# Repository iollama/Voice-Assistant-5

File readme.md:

# Voice Assistant 5 — STEM Oriented ESP32 Voice Assistant With No Personality

Press the button, talk, let go — and get an instant spoken reply, with an animated emoji face that grins, frowns and laughs along with the conversation. Less than $20 in parts, a case you print yourself, running on your own OpenAI key.

The part that makes it worth building: **it has no character until you give it one.**

Everything that gives this thing a personality lives behind a web page the device serves. The ~~system~~ persona prompt, one of ten voices, the spoken language, and the face itself:
drop in a GIF, PNG, JPG or MP4 and it adopts immediately. No recompile, no cable, no SD card, no code. Write Nietzsche. Write Churchill. Write Daffy Duck. Hand it to someone else and let them write over it.

That design came out of a classroom. VA5 is used in schools, where students research a figure, write the persona themselves, load it on, and then have to
hold a conversation with what they wrote. A thin characterisation falls apart within a minute or two of being interrogated, so they go back and rewrite it.
Write, test by talking, revise — which is prompt engineering, except nobody has to call it that.

Thirty students cannot each be flashing firmware. That single constraint explains most of the design decisions in this repo: why the whole persona is editable from a phone, and why personas export as a `.zip` so one set of
devices can cycle between classes.

## Features

- **Press to talk, get an instant reply** -- hold the button to speak, release and it answers right back (no wake word, no waiting)
- **Animated emoji face shows you how the assistant feels** -- the assistant itself picks the mood and the display reacts in real time
- **Control the assistant personality** -- write who it is and how it behaves, right from your phone, no code needed
- **Glance to know what it's doing** -- a colored light tells you when it's listening, thinking, or speaking
- **The assistant adjusts its own volume** -- say "speak up" or "quieter please" and it adjusts in real time; the new level persists across reboots
- **Plug in your own OpenAI key** -- you control the account and the cost, no subscription in the middle
- **Make the face your own** -- drop in a GIF, PNG, JPG, or MP4 from the web portal and the assistant uses it as the on-device emoji; reset back to the defaults any time
- **It remembers the conversation** -- pick up where you left off instead of starting from scratch
- **Set up WiFi once, anywhere** -- connect from your phone the first time; it remembers up to 6 networks and picks the right one wherever you take it
- **Build it yourself for ~$20** -- 3D-printed case included, full source open and hackable, parts links provided

## Initial Setup

1. **Connect to the device's WiFi.** On first boot the assistant creates an open WiFi network named `VOICE-AGENT-XXYY` (the `XXYY` is the last 2 bytes of its MAC address). No password.
2. **Set your home WiFi.** Your phone should pop the captive portal automatically -- if not, open a browser and go to `http://192.168.4.1`. Under **Wi-Fi Networks**, enter your network name and password, hit **Add network**, then **Connect & reboot**. The device remembers it from then on -- and up to five more.
3. **Open the settings page.** Once it's on your network, browse to `http://voice-agent-XXYY.local` (same `XXYY` as the AP name). If `.local` doesn't resolve on your network, use the IP address printed to the Serial Monitor.
4. **Make it your own.** By default the assistant is obsessed with Pokémon and will work them into every reply -- charming for about ten minutes. Edit the **System Prompt** field on the settings page to give it any persona you like.

## Under the Hood

A push-to-talk voice assistant built on the ESP32-S3, using the OpenAI Realtime API for speech-to-speech conversation over secure WebSockets. Features dual-core FreeRTOS architecture, animated emoji display with audio waveform visualization, a web configuration portal, and RGB LED status indicators.

Core 0 handles all network and protocol tasks (WiFi, WebSocket, Base64 encode/decode). Core 1 handles all hardware I/O (I2S microphone/speaker, button, display). The two cores communicate through PSRAM ring buffers and volatile flags.

The assistant can also call **OpenAI function tools** during a response — currently `set_display_emotion` (drives the emoji display), `set_volume` (adjusts speaker volume, persists across reboots), and `show_network_info` (shows the device IP and token count on screen).

## Hardware Components

| Component | Description | Comments | Link |
|-----------|-------------|----------|------|
| ESP32-S3 N16R8 | Dev board with 16 MB flash and 8 MB OPI PSRAM |buy the N16R8 varient | [Ali](https://s.click.aliexpress.com/e/_c3gDaUQx), [Amazon](https://amzn.to/4epGav2) |
| INMP441 | I2S MEMS microphone | - | [Ali](https://s.click.aliexpress.com/e/_c4aRLzSX), [Amazon](https://amzn.to/4tT7aI8) |
| MAX98357A | I2S audio amplifier breakout | Better to buy soldered| [Ali](https://s.click.aliexpress.com/e/_c3a1cRKJ), [Amazon](https://amzn.to/4w4aq4O) |
| PCM5102A (optional) | I2S DAC breakout (GY-PCM5102A) with 3.5 mm stereo jack | Skip if you only want the onboard speaker. Drives headphones or any powered speaker (e.g. JBL Go/Clip/Flip) via a 3.5 mm AUX cable. | [Ali](https://s.click.aliexpress.com/e/_c3kweqLP), [Amazon](https://amzn.to/4dvBhQi) |
| Speaker | 1-3W 4/8-ohm or similar small speaker | Up to 57mm, use foam for pressure if the speaker is too thin | [Ali](https://s.click.aliexpress.com/e/_c4tSecWd), [Amazon](https://amzn.to/49pMOhj) |
| GC9A01 | Round TFT display, 240x240, SPI | Get the square one | [Ali](https://s.click.aliexpress.com/e/_c3MHXSVp), [Amazon](https://amzn.to/3RhVD6A) |
| WS2812 NeoPixel | RGB LED (built-in on most ESP32-S3 dev boards) | Nothing to buy, it's built in | - |
| Tactile Push Button | 12x12 mm momentary switch (PTT) | - | [Ali](https://s.click.aliexpress.com/e/_c3t0W2xV), [Amazon](https://amzn.to/4unYv0b) |
| Jumper Wires | Male-to-male/female (for the non PCB version) | - | [Ali](https://s.click.aliexpress.com/e/_c32s7dYx), [Amazon](https://amzn.to/48EsDvR) |
| USB-C Cable | Data + power, Type C to Type A | You should have one at home | [Ali](https://s.click.aliexpress.com/e/_c4mijwjN), [Amazon](https://amzn.to/3QNDeyr) |
| Breadboard | 400 Tie Points |You'll only need one power rail | [Ali](https://s.click.aliexpress.com/e/_c3MZmHuT), [Amazon](https://amzn.to/4w8xcZr) |
| Screws | M2 and M3 Self-Tapping Screws | I recommend a full kit | [Ali](https://s.click.aliexpress.com/e/_c3LsKZUF), [Amazon](https://s.click.aliexpress.com/e/_c3LsKZUF) |

## Personas
A persona is a character the device becomes: a system prompt, a voice, a language and an emoji set, bundled together. The settings page has a **Browse** gallery that pulls ready-made ones straight from this repo, and you can export your own as a `.zip` to back up, share, or hand to a class.

Shipped categories include Science (Ada Lovelace, Marie Curie, Sir Isaac Newton), Historical (Abraham Lincoln, Winston Churchill) and Philosophy (Friedrich Nietzsche, Yoda, Daffy Duck) — alongside Biblical, Theological, and a Functional category holding an ESP32 that explains its own hardware.

Writing your own is the interesting part. Vague personas produce vague conversations — the difference between "you are Winston Churchill" and a paragraph on what he knew, how he spoke, what he refused to discuss and where
he was wrong is immediately audible.

Personas live in [`personas/`](personas). Pull requests welcome.

There is also a persona-creating skill for Google's Antigravity in [`.agents/skills/persona-creator/`](.agents/skills/persona-creator/) — the same workflow the personas above were built with.

## Custom PCB (Optional)

Don't want to breadboard it? [`pcb/`](pcb/) has a custom 2-layer breakout PCB that wires up the same components fixed pin-for-pin (matching the tables below) and adds a solder-in expansion header for spare GPIOs. This is the exact board design that was ordered, assembled, and is running the unit here at VA5 HQ — not an unverified first spin.

What's in `pcb/`:
- **`va5pcb.kicad_pcb` + `va5pcb.kicad_pro`** -- the KiCad board project. Open it in [KiCad](https://www.kicad.org/) (8.0+) to inspect footprint placement, silkscreen, or the routed copper before ordering.
- **`fab/`** -- bare-board gerbers + Excellon drill (`*.gbr`, `*.drl`, `.gbrjob`), already exported and ready to hand to a fab house (JLCPCB, PCBWay, etc.) as-is. Standard 2-layer board, no unusual stackup.

The board was scripted-routed then hand-finished in KiCad (a couple of stragglers a headless autorouter leaves behind); run your own DRC pass in KiCad if you want to double-check before ordering. The parametric generator that produced this board (component placement, net list, silkscreen) isn't part of this release -- `pcb/` ships the finished design, not the pipeline that built it.

Populate it with the same parts as the [Hardware Components](#hardware-components) table above (skip the breadboard and jumper wires -- solder straight onto the board footprints instead). The PCM5102A headphone DAC is optional, same as the breadboard build; if you install it, use the **PCB build** parts (`pcb_ring.stl`, `pcb_top.stl`, `pcb_bottom.stl`) from [3D Printed Enclosure](#3d-printed-enclosure) below, which carry a matching 3.5 mm jack hole in the ring. The board's spare-GPIO header is documented in [Expansion Header (PCB build only)](#expansion-header-pcb-build-only) below.

## Pin Assignments

### Microphone -- INMP441

| INMP441 Pin | ESP32-S3 Pin | Note |
|-------------|-------------|------|
| SD (data) | GPIO 40 | I2S data in |
| WS | GPIO 41 | Word select / LRCLK |
| SCK | GPIO 42 | Bit clock |
| L/R | GND | Selects left channel |
| VDD | 3.3V | |
| GND | GND | |

### Speaker Amplifier -- MAX98357A

| MAX98357A Pin | ESP32-S3 Pin | Note |
|--------------|-------------|------|
| DIN | GPIO 17 | I2S data out (shared with PCM5102A if both populated) |
| BCLK | GPIO 47 | Bit clock (shared) |
| LRC | GPIO 21 | Word select / LRCLK (shared) |
| SD | 3.3V *or* GPIO 38 | 3.3V keeps the amp always on (legacy wiring). Tie to GPIO 38 instead if you've also populated the PCM5102A and want to switch between them from the portal. |
| VIN | 5V | |
| GAIN | 3.3V | 6 dB gain (recommended) -- avoids amp clipping/distortion into an 8 Ω speaker at high volume |
| GND | GND | |

### Headphone DAC (optional) -- PCM5102A

Populate this only if you want a headphone jack or want to feed a powered speaker (e.g. JBL) via 3.5 mm AUX. With both chips installed, the portal *Audio Output* selector picks which one plays; firmware mutes the other via its enable pin.

| PCM5102A Pin | ESP32-S3 Pin | Note |
|--------------|-------------|------|
| DIN | GPIO 17 | I2S data out (shared with MAX98357A) |
| BCK | GPIO 47 | Bit clock (shared) |
| LCK | GPIO 21 | Word select / LRCLK (shared) |
| SCK | GND | Use internal PLL (no MCLK from ESP32) |
| XSMT | GPIO 39 | Active-low mute; HIGH = play |
| FMT, FLT, DEMP | GND (factory-set on most breakouts) | I2S format, normal filter, no de-emphasis |
| VIN | 3.3V | Most GY breakouts accept 3.3V or 5V; check silkscreen |
| GND | GND | |
| L / R / GND | 3.5 mm stereo jack | Built into the breakout PCB |

The portal *Audio Output* selector (below *Volume*) picks Speaker (MAX98357A) or Headphones (PCM5102A). The choice persists across reboots. Changes are rejected with HTTP 409 during an active conversation -- save while idle (green LED).

You can also just say *"switch to headphones"* or *"use the speaker"*. VA5 confirms on the current output and switches right after that reply. A small speaker / headphones icon above the on-screen volume bar shows where audio is going. (Without a PCM5102A installed, "headphones" goes silent; say *"switch back to the speaker"* to undo.)

### Display -- GC9A01

| GC9A01 Pin | ESP32-S3 Pin | Note |
|------------|-------------|------|
| SCLK | GPIO 6 | SPI clock |
| MOSI (SDA) | GPIO 7 | SPI data |
| CS | GPIO 5 | Chip select |
| DC | GPIO 4 | Data/command |
| RST | GPIO 2 | Hardware reset |
| BLK | 3.3V | Backlight (always on) |
| VCC | 3.3V | |
| GND | GND | |

### Other

| Component | Pin | ESP32-S3 Pin | Note |
|-----------|-----|-------------|------|
| PTT Button | Signal | GPIO 1 | INPUT_PULLUP, active LOW |
| PTT Button | GND | GND | |
| NeoPixel RGB LED | Data | GPIO 48 | Built-in on most S3 boards, no jumper needed. Also brought out on the expansion header (see below) for future repurposing. |
| MAX98357A SD (optional) | Enable | GPIO 38 | Only needed if you populated the PCM5102A and want runtime switching. Otherwise tie SD to 3.3V. |
| PCM5102A XSMT (optional) | Mute | GPIO 39 | Only populated when PCM5102A is installed. HIGH = play, LOW = mute. |

### Power Summary

| Rail | Components |
|------|-----------|
| 3.3V | INMP441, GC9A01, MAX98357A SD pin (legacy wiring only), GC9A01 BLK, PCM5102A VIN (optional) |
| 5V | MAX98357A VIN |
| GND | All components (common ground) |

### Expansion Header (PCB build only)

The PCB build exposes every ESP32-S3 GPIO that isn't already driven by a peripheral, plus power rails, on unpopulated 2.54 mm through-hole pads. Solder a male or female header strip if you want one — pick whichever fits your add-on. Most pads sit in the lower band of the board; four GPIOs are on a small **screen-side** header in the gap between the ESP and the display.

| Header | Pads | Silkscreen labels |
|---|---|---|
| Data — bottom (J9) | 8 GPIO | `9 48 10 11 12 13 14 19` |
| Data — screen-side (J13) | 4 GPIO | `15 16 18 8` |
| Power — bottom (J10) | 7 | `3V 3V G G G 5V 5V` (2×3.3 V / 3×GND / 2×5 V) |

Notes on the data row:
- The four ESP32-S3 boot-strapping pins (GPIO 0, 3, 45, 46) are **not** broken out — they have boot-time constraints, so the header exposes only freely-usable GPIO.
- GPIO 19 is also the chip's native USB D−. GPIO 20 (the other native USB line, D+) is **not** broken out on this header. If a future build uses the chip's native USB, GPIO 19 becomes unavailable too.
- GPIO 48 is the on-module RGB status LED. It's brought out for future repurposing, but anything you wire to it will fight the firmware's status indicator until you disable that path in code.

Silkscreen labels are shortened (`3V` rather than `3V3`, `G` rather than `GND`) so each label fits within the 2.54 mm pad pitch.

## Build Toolchain

Pick **one** of the two toolchains below -- both build the same `.ino` source. Versions are pinned in [toolchain.md](toolchain.md).

### Option A -- Arduino IDE

Set these under the **Tools** menu before uploading:

| Setting | Value |
|---------|-------|
| **Board** | ESP32S3 Dev Module |
| **USB CDC On Boot** | Enabled |
| **CPU Frequency** | 240MHz (WiFi) |
| **Core Debug Level** | None |
| **USB DFU On Boot** | Disabled |
| **Erase All Flash Before Sketch Upload** | Disabled |
| **Events Run On** | Core 1 |
| **Flash Mode** | QIO 80MHz |
| **Flash Size** | 16MB (128Mb) |
| **JTAG Adapter** | Disabled |
| **Arduino Runs On** | Core 1 |
| **USB Firmware MSC On Boot** | Disabled |
| **Partition Scheme** | Custom (uses `partitions.csv` from sketch folder) |
| **PSRAM** | OPI PSRAM |
| **Upload Mode** | UART0 / Hardware CDC |
| **Upload Speed** | 921600 |
| **USB Mode** | Hardware CDC and JTAG |

The custom partition table (`partitions.csv`) provides 3 MB for the app and ~11 MB for LittleFS (emoji frames).

Install libraries via Arduino Library Manager (`Sketch > Include Library > Manage Libraries...`):

| Library | Author | Note |
|---------|--------|------|
| **ArduinoJson** (v6.x+) | Benoit Blanchon | JSON parsing for API messages |
| **Adafruit NeoPixel** | Adafruit | RGB status LED driver |
| **Arduino_GFX_Library** | moononournation | Display driver (required only when `USE_DISPLAY 1`) |

QR codes (captive-portal join + network info screen) use the `esp_qrcode` API bundled with the ESP32 board package -- no separate library install.

**ArduinoWebsockets** is **vendored** in the `src/` directory with two critical bug fixes applied. Do **not** install it via Library Manager -- the sketch includes the local patched copy automatically. See [websockets_patches.md](voice_agent_5/docs/websockets_patches.md) for details.

### Option B -- PlatformIO

Everything (board settings, partition scheme, libraries, build flags) is pinned in [platformio.ini](platformio.ini). After cloning and copying `config.h.sample` to `config.h` (see below):

```bash
pio run -t upload          # compile + upload sketch
pio run -t uploadfs        # upload LittleFS data partition (emoji frames)
pio device monitor         # serial monitor at 115200, with esp32 exception decoder
```

Or, in VS Code, install the **PlatformIO IDE** extension and use the toolbar buttons (Build / Upload / Upload Filesystem Image / Serial Monitor).

`platformio.ini` uses the [pioarduino](https://github.com/pioarduino/platform-espressif32) fork of the espressif32 platform -- the default upstream platform is stuck on Arduino-ESP32 core 2.x and is missing a header that `Arduino_GFX_Library` 1.6.5 needs. The pin `55.03.312-1` matches Arduino-ESP32 3.3.12.

The vendored ArduinoWebsockets is found via PlatformIO's `src_dir = voice_agent_5` setting -- do not add `arduinoWebsockets` to `lib_deps`.

## Configuration

### config.h

A `config.h.sample` file is included in the sketch folder. Copy it to `config.h` and fill in your credentials:

```bash
cp voice_agent_5/config.h.sample voice_agent_5/config.h
```

Then edit `config.h` and replace the placeholder values with your OpenAI API key (and optionally WiFi credentials):

```cpp
#define OPENAI_API_KEY "sk-your-openai-api-key"
#define WIFI_SSID "your-network-name"
#define WIFI_PASSWORD "your-network-password"
```

`config.h` is listed in `.gitignore` and will not be committed. WiFi credentials are also configurable at runtime via the captive portal and stored in NVS. The API key can also be set via the web UI (stored in NVS, overrides `config.h`).

### WiFi Setup (Captive Portal)

1. On first boot (or when none of the saved networks can be reached), the device creates a WiFi access point named `VOICE-AGENT-XXYY` (last 2 bytes of MAC)
2. The RGB LED flashes yellow to indicate configuration mode
3. The display shows a WiFi QR code and join instructions — scan it with your phone to join the network automatically
4. A captive portal page opens automatically (or navigate to `192.168.4.1`)
5. Under **Wi-Fi Networks**, enter your network name and password and click **Add network** (or press **Scan** and pick it from the list), then **Connect & reboot**
6. The device restarts and connects to your WiFi network
7. Once connected, the display shows the IP address and a QR code — scan it or enter the IP in a browser to reach the settings page
8. The RGB LED turns green when ready

**Shortcut:** hold the push-to-talk button while powering the device on to go straight to the config portal, without waiting for it to try the saved networks first.

### Multiple WiFi Networks

The device remembers up to **6 networks**, so it can move between home, the office and a phone hotspot without being set up again.

- **At power-on** it scans, then joins the most recently used saved network that is in range. If that one fails it tries the next, and so on; only when they have all failed does it open the config portal. The display names each network as it tries it.
- **A failed connection never erases the network.** An AP that was simply switched off stays in the list.
- **Add networks ahead of time.** You can save a network you are nowhere near — type its name and password, and it will be used the next time it is in range. Adding a network does not reboot the device or disturb the current connection.
- **Full list?** Saving a seventh network drops the least recently used one to make room, and the page tells you which one went. Networks you have saved but never actually connected to are dropped first.
- **Switching now.** Press **Connect** on any saved network to reboot into it. The device attempts that exact network first, whether or not it showed up in a scan. If it can't be reached, it falls back to its usual order rather than refusing, and tells you so when you next load the settings page: *"Couldn't reach UdisS24P — still on Tirosh-g."* **Forget** removes one; forgetting the network you are currently using does not cut you off, it just stops the device from choosing it again.

Passwords are stored on the device and are never shown again — not on the settings page and not through its API. They are, however, stored unencrypted in the ESP32's NVS flash, so treat physical access to the board as access to those passwords.

### Agent Settings (Web Portal)

Once connected to WiFi, open a browser and navigate to `http://voice-agent-XXYY.local` (or the IP address printed to Serial Monitor).

From the settings page you can configure:

- **System Prompt** -- Control the assistant's persona and response style
- **Voice** -- One of the 10 OpenAI Realtime voices (`marin`, `cedar`, `alloy`, `ash`, `ballad`, `coral`, `echo`, `sage`, `shimmer`, `verse`); selection takes effect on the next session
- **Language** -- The language the assistant speaks. Default **Automatic** matches whatever language you speak; pick a specific language to force every reply into it. Takes effect on the next session
- **Volume** (0 - 100%) -- Speaker playback volume
- **Audio Output** -- Speaker or Headphones (only if the optional PCM5102A DAC is installed)
- **Import / Export Profile** -- **Browse** a gallery of ready-made personas, or back up / transfer your own persona, voice, volume and emoji as a single `.zip` file. Secrets (Wi-Fi, API key) are never exported. Needs the browser to be online. See [voice_agent_5/docs/profile-import-export.md](voice_agent_5/docs/profile-import-export.md).

Less-common options live behind the **Admin Zone** toggle further down the page: **Wi-Fi Networks** (see [Multiple WiFi Networks](#multiple-wifi-networks) above), your **API Key** (override the compiled `config.h` key, stored in NVS), conversation behavior (Persist Conversation, Verbose Logging), and token usage.

All settings are saved to NVS and persist across reboots. Use **Restore defaults** (in the Admin Zone) to reset the agent settings.

The Admin Zone also has **Provision default persona**, which pulls the published default persona -- prompt, voice and emoji -- from the project repo and writes it into the device. Use it to set up a board that was flashed with firmware but no emoji image (so the display would otherwise be blank), or to load a newly published default. Unlike **Restore defaults** (which reverts to the compiled-in fallback prompt and on-device emoji), this downloads the current default from the web, so your browser needs internet. It writes the device's read-only default emoji set directly and checks free storage before changing anything.

## Emoji Display Setup

### Prerequisites

- GC9A01 display wired per the pin table above
- `USE_DISPLAY` set to `1` in `voice_agent_5.ino` (default)
- Arduino_GFX_Library available (Library Manager for Arduino IDE; auto-resolved from `lib_deps` for PlatformIO)

### Replacing Emojis from Your Browser

Once the device is on WiFi, browse to `http://voice-agent-XXYY.local/emojis` (or hit **Open editor** on the main settings page). Drop in a GIF, PNG, JPG, or H.264 MP4 for any of the seven moods and the assistant will use it immediately -- no re-flash, no Python, no SD card. The shipped defaults are stored separately and are never overwritten, so there is no way to brick the device through customization; reset any mood (or all of them) at any time. See [voice_agent_5/docs/emoji-customization.md](voice_agent_5/docs/emoji-customization.md) for the full walkthrough, supported formats, and how to share an emoji pack.

The customization page needs your browser to have internet access (it loads the GIF decoder and zip libraries from a CDN). The device itself stays local-only.

### Uploading the LittleFS Filesystem

The emoji animations are stored as pre-rendered RGB565 binary frames in a LittleFS partition. They must be flashed separately from the sketch. The sketch and filesystem go to different partitions -- they don't overwrite each other. You only need to re-upload the filesystem when the frame files change.

**With PlatformIO:**

```bash
pio run -t uploadfs
```

`platformio.ini` already points `data_dir` at `voice_agent_5/data/`, so this packages the 56 `.bin` frame files into a LittleFS image and flashes it to the data partition.

**With Arduino IDE** (one-time plugin install):

1. Go to https://github.com/earlephilhower/arduino-littlefs-upload/releases
2. Download the latest `.vsix` file
3. Copy it to `~/.arduinoIDE/plugins/` (create the `plugins` folder if it doesn't exist)
4. Restart Arduino IDE

Then to upload:

1. Close the Serial Monitor (it locks the COM port)
2. Press **Ctrl+Shift+P** to open the Command Palette
3. Type **Upload LittleFS** and select **"Upload LittleFS to Pico/ESP8266/ESP32"**
4. Wait for it to finish

**Verify:** Open Serial Monitor after uploading both sketch and filesystem. You should see:

```
LittleFS mounted.
Display: loaded 8 frames for 'neutral'
Display: GC9A01 initialized
```

### Re-generating Emoji Frames (Optional)

If you want to regenerate the `data/*.bin` files from the source GIFs in `feelings/`:

**Requirements:** Python 3 with Pillow (`pip install Pillow`)

**Run:**

```bash
cd voice_agent_5
python utils/convert_gifs.py
```

This extracts 8 evenly-spaced frames from each GIF, resizes to 150x150, converts to RGB565 little-endian binary, and writes to `data/default/<emotion>_<frame>.bin`. The `default/` subdirectory is the shipped emoji set; runtime overrides written from the captive portal land in `data/custom/` on the device and never touch the defaults.

### Emoji Credits

Emoji animations sourced from [Google Fonts Emoji](https://googlefonts.github.io/), used under the [Creative Commons Attribution 4.0 International License (CC BY 4.0)](https://creativecommons.org/licenses/by/4.0/legalcode).

## Library Patches

ArduinoWebsockets v0.5.4 has two upstream bugs that prevent WSS connections on ESP32: a missing `setInsecure()` method in `SecuredEsp32TcpClient`, and a missing fallback to insecure mode in the ESP32 branch of `upgradeToSecuredConnection()`. Both cause every secure WebSocket connection to fail silently. (Both are still present upstream as of v0.5.4.)

The library is vendored in `src/` with fixes already applied -- no manual patching required. For full details, the exact code changes, and instructions for updating to a newer version, see [websockets_patches.md](voice_agent_5/docs/websockets_patches.md). For the licensing side -- upstream version, licence, and the full list of what was modified -- see [VENDORED.md](voice_agent_5/src/VENDORED.md).

## Tuning Knobs

### Compile-Time Constants

These are defined in `voice_agent_5.ino` and require recompilation to change:

| Constant | Default | Description |
|----------|---------|-------------|
| `SAMPLE_RATE_IN` | 24000 | Microphone sample rate (Hz). Required by the OpenAI Realtime GA API (`audio/pcm` is fixed at 24 kHz). |
| `SAMPLE_RATE_OUT` | 24000 | Speaker playback rate (Hz). Must match OpenAI Realtime API output format. |
| `JITTER_BUFFER_MS` | 300 | Milliseconds of audio to buffer before starting playback. Higher = smoother but more latency. |
| `LOW_WATER_BYTES` | 3072 | Rebuffer threshold (~64 ms at 24 kHz). When the speaker buffer drops below this during playback, pause and re-accumulate before resuming. |
| `DMA_BLOCK_SIZE` | 1024 | I2S DMA transfer size in bytes per read/write call. |
| `WIFI_CONNECT_TIMEOUT_MS` | 8000 | Time to wait for each saved network in range before trying the next one. |
| `WIFI_SOLE_TIMEOUT_MS` | 15000 | Time to wait when exactly one saved network is in range — there is nothing to fall through to but the config portal, so it gets a longer budget. |
| `WIFI_MAX_NETWORKS` | 6 | How many WiFi networks are remembered (in `wifi_store.h`). Saving another drops the least recently used one. |
| `EMOJI_FRAME_MS` | 120 | Delay between emoji animation frames (~8 fps). Lower = faster animation. |
| `EMOJI_SIZE_PX` | 150 | Emoji frame dimensions (width and height). Must match `convert_gifs.py` output. |
| `EMOJI_NUM_FRAMES` | 8 | Number of animation frames per emotion. Must match `convert_gifs.py` output. |
| `USE_DISPLAY` | 1 | Set to `0` to disable display entirely (serial-only mode, no GC9A01 or Arduino_GFX needed). |

### Runtime Settings (Web UI / NVS)

These are configurable at runtime via the web portal and persist across reboots:

| Setting | Default | Range | Description |
|---------|---------|-------|-------------|
| System Prompt | "You are a helpful voice assistant..." | up to 12 KB (12288 chars) | Controls assistant persona |
| Voice | `marin` | `alloy`, `ash`, `ballad`, `coral`, `echo`, `sage`, `shimmer`, `verse`, `marin`, `cedar` | OpenAI Realtime voice; applies on next session |
| Language | Automatic | Automatic or one of 13 languages | Forces every reply into the chosen language; Automatic matches whatever you speak. Applies on next session |
| Persist Conversation | true | boolean | Chain responses via `previous_response_id` |
| Verbose Logging | true | boolean | Detailed serial debug output |
| Volume | 50 | 0 - 100 | Speaker volume (PCM sample scaling) |
| Audio Output | Speaker | Speaker / Headphones | Which output plays (only meaningful with the optional PCM5102A installed) |

## 3D Printed Enclosure

The `box/` directory contains the STL files for a circular 145 mm enclosure designed to hold all components. The geometry is a parametric [build123d](https://github.com/gumyr/build123d) (Python) model; the `.stl` files here are pre-generated from it, so you don't need to render anything yourself.

Each printable part is its own STL, and the file prefix tells you which build it belongs to — print every `3dp_*` file **or** every `pcb_*` file, never a mix. No part is shared between the two builds.

- **Breadboard / jumper-wire build (`3dp_*`, 7 parts):** `3dp_ring.stl` (carries the same 3.5 mm jack passthrough as the PCB ring, for the optional PCM5102A), `3dp_top.stl` (the top plate carries printed bosses for the ESP32, display, amp, mic, speaker, and button), `3dp_bottom.stl`, plus the small parts that mount components to the top plate: `3dp_speaker_y_bracket.stl`, `3dp_cantilever_bracket.stl` (ESP32 clamp), `3dp_inline_button_frame.stl`, and `3dp_inline_button_bracket.stl`.
- **PCB build (`pcb_*`, 3 parts):** `pcb_ring.stl` (includes a 3.5 mm jack passthrough aligned with the optional PCM5102A DAC), `pcb_top.stl` (completely flat — the speaker is glued, so there are no bosses), `pcb_bottom.stl` (carries four standoffs that set the PCB height above the bottom plate).

The parametric build123d source (where dimensions, component positions, and clearances are defined) is maintained in the project's development repo and isn't bundled with this release — just pick the STL set matching your build above and print.

The design uses a top/ring/bottom construction: the **top** plate holds all components (ESP32, display, speaker, mic, amplifier, button) facing **down** into the body — from outside you see its flat face. It is printed feature-side-up and flipped over at assembly; the model is pre-mirrored so that, once flipped, everything lines up with the PCB below. The ring forms the enclosure wall (USB cutout toward the ESP; orient the headphone hole toward the bottom), and the **bottom** plate closes the base. Parts are secured with M3 screws into printed bosses.

## State Machine / LED Colors

| State | LED Color | Meaning |
|-------|-----------|---------|
| `STATE_WIFI_WAIT` | Yellow (solid) | Connecting to WiFi |
| `STATE_WIFI_CONFIG` | Yellow (flashing) | AP mode, awaiting WiFi credentials |
| `STATE_READY_FOR_INPUT` | Green | Idle, ready for push-to-talk |
| `STATE_RECORDING` | Pink | Mic active, streaming audio to OpenAI |
| `STATE_THINKING` | Blue | Waiting for API response |
| `STATE_SPEAKING` | Cyan | Playing response audio |

## Adding a Tool

Tools are OpenAI function calls the model makes autonomously during a response. All tool registration lives in `voice_agent_5/tools.ino` — adding a tool is two steps and touches only that one file.

**Step 1 — Write the handler:**

```cpp
static void handleMyToolCall(const String& payload) {
    DynamicJsonDocument doc(256);
    if (deserializeJson(doc, payload) != DeserializationError::Ok) return;

    beginToolCall(doc["call_id"] | "");   // sets up g_pending_call_id and flags

    // parse arguments, do your work, optionally set g_tool_result_output
    g_tool_result_output = "done";
}
```

> **Important:** handlers run inside the WebSocket `onMessage` callback and cannot call `wsClient.send()` directly. Use the flag mechanism (`beginToolCall` + `g_tool_result_output`) — the protocol loop sends the result after `response.done` arrives. For cross-core side effects (display, NVS writes), set a `volatile bool` flag and handle it on Core 1 in `loop()`.

**Step 2 — Register the tool:**

Add an entry to the `TOOLS[]` array in `tools.ino`:

```cpp
{
    "my_tool_name",
    "Plain-text description the model reads to decide when to call this.",
    "{\"type\":\"object\",\"properties\":{"
    "\"param1\":{\"type\":\"string\",\"description\":\"What param1 does\"}"
    "},\"required\":[\"param1\"]}",
    handleMyToolCall
}
```

`buildToolsJson()` will include the new schema in the next `session.update`, and `dispatchToolCall()` will route calls to your handler. No changes to `protocol.ino` needed.

For the full async tool call flow diagram, see [voice_agent_5/docs/architecture.md](voice_agent_5/docs/architecture.md#how-to-add-a-new-tool).

## Architecture Documentation

For detailed technical documentation covering dual-core architecture, ring buffer internals, audio pipeline, protocol details, emoji display system, and memory layout, see [architecture.md](voice_agent_5/docs/architecture.md).

## Troubleshooting

- **LED stays yellow**: the device is still working through its saved WiFi networks. It tries each one that is in range for 8 seconds before falling back to SoftAP config mode, so with six saved networks this can take about a minute. Hold the push-to-talk button while powering on to skip straight to the config portal.
- **No sound from speaker**: Verify the MAX98357A SD pin is connected to 3.3V (not GND).
- **Microphone not picking up audio**: Check INMP441 wiring (especially L/R to GND for left channel).
- **Can't reach `.local` address**: mDNS may not work on all networks/devices. Use the IP address printed to Serial Monitor instead.
- **Display shows text instead of emoji**: LittleFS filesystem not uploaded, or frame files missing. Re-upload the filesystem using the LittleFS plugin.
- **"Display: gfx->begin() FAILED!"**: Check display SPI wiring (especially DC, CS, RST pins).

## License

VA5 is licensed under [GPL-3.0](LICENSE) (GNU General Public License, version 3).

You can build these devices, use them, modify them, teach with them, and sell them. None of that needs anyone's permission. If you'd like to talk about a commercial arrangement or a classroom deployment, you're welcome to — hello@oriliventures.com — but it isn't a condition of any of the above.

The obligation that comes with GPL-3.0 is share-alike: if you hand someone the firmware, or a device running it, modified or not, they're entitled to the source under this same licence.

### Third-party components

- **ArduinoWebsockets** — a *modified* copy of [gilmaimon/ArduinoWebsockets](https://github.com/gilmaimon/ArduinoWebsockets) v0.5.4 is vendored in [voice_agent_5/src/](voice_agent_5/src/). It is GPL-3.0, and that is why this project is GPL-3.0. What was changed and why: [VENDORED.md](voice_agent_5/src/VENDORED.md); the exact patches: [websockets_patches.md](voice_agent_5/docs/websockets_patches.md).
- **Emoji animations** — from [Google Fonts Emoji](https://googlefonts.github.io/), under [CC BY 4.0](https://creativecommons.org/licenses/by/4.0/legalcode).
- **base64 encoder** — © 2004-2008 René Nyffenegger, zlib-style licence, notice retained in `voice_agent_5/src/tiny_websockets/internals/wscrypto/base64.hpp`.
- **SHA-1 implementation** — from [983/SHA1](https://github.com/983/SHA1), credit retained in `voice_agent_5/src/tiny_websockets/internals/wscrypto/sha1.hpp`.

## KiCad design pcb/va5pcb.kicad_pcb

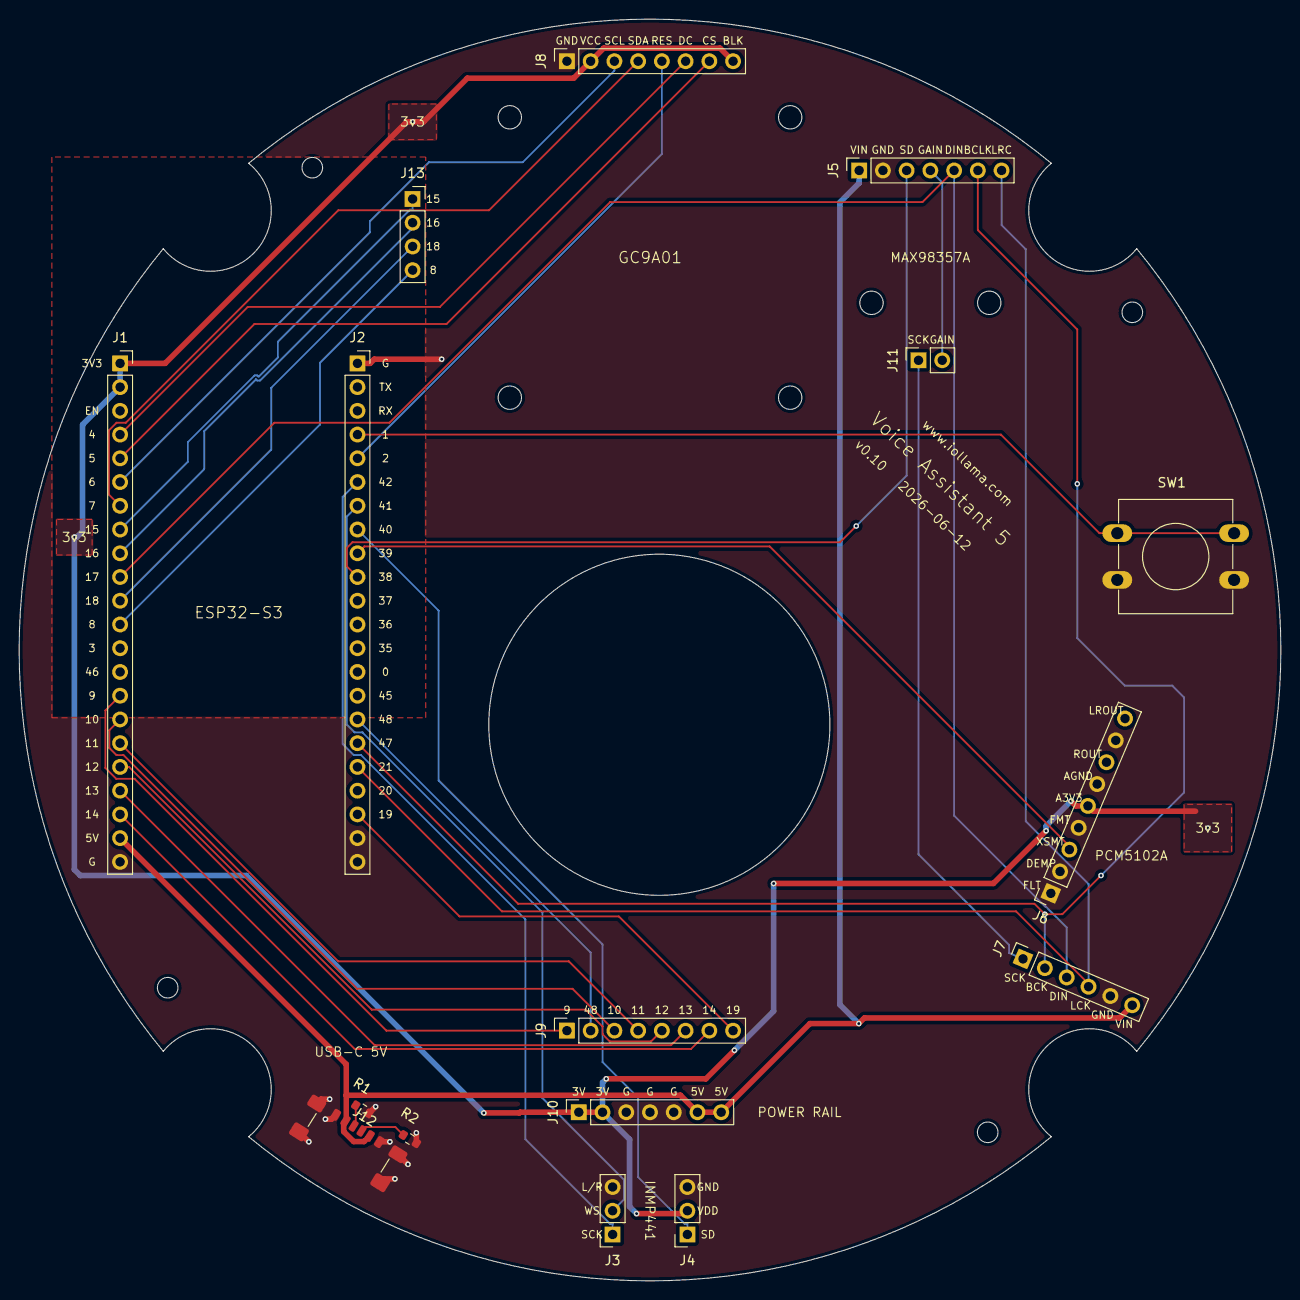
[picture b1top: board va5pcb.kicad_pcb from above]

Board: 2 copper layers, 135.0 x 135.0 mm, 16 parts (0 on the bottom side), 33 nets.

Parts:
J1, J2: ESP32-S3; PinSocket_1x22_P2.54mm_Vertical
J3, J4: INMP441; PinSocket_1x03_P2.54mm_Vertical
J5: MAX98357A; PinSocket_1x07_P2.54mm_Vertical
J6: PCM5102A; PinSocket_1x09_P2.54mm_Vertical
J7: PCM5102A; PinSocket_1x06_P2.54mm_Vertical
J8: GC9A01; PinSocket_1x08_P2.54mm_Vertical
J9: EXP-DATA; PinSocket_1x08_P2.54mm_Vertical
J10: EXP-PWR; PinSocket_1x07_P2.54mm_Vertical
J11: EXP-AUX; PinSocket_1x02_P2.54mm_Vertical
J12: USB-C 5V; USB_C_Receptacle_GCT_USB4135-GF-A_6P_TopMnt_Horizontal
J13: EXP-SCR; PinSocket_1x04_P2.54mm_Vertical
R1, R2: USB-C 5V; R_0603_1608Metric
SW1: PTT; SW_PUSH-12mm

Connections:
3V3: J1.1, J1.2, J4.2, J6.5, J8.2, J8.8, J10.1, J10.2
5V: J1.21, J5.1, J7.6, J10.6, J10.7, J12.A9, J12.B9
AUDIO_MAX_SD: J2.10, J5.3
AUDIO_PCM_XSMT: J2.9, J6.3
CC1: J12.A5, R1.1
CC2: J12.B5, R2.1
EXP_GPIO8: J1.12, J13.4
EXP_GPIO9: J1.15, J9.1
EXP_GPIO10: J1.16, J9.3
EXP_GPIO11: J1.17, J9.4
EXP_GPIO12: J1.18, J9.5
EXP_GPIO13: J1.19, J9.6
EXP_GPIO14: J1.20, J9.7
EXP_GPIO15: J1.8, J13.1
EXP_GPIO16: J1.9, J13.2
EXP_GPIO18: J1.11, J13.3
EXP_GPIO19: J2.20, J9.8
EXP_GPIO48: J2.16, J9.2
GND: J1.22, J2.1, J2.21, J2.22, J3.3, J4.3, J5.2, J6.1, J6.2, J6.4, J6.6, J6.8, J7.5, J8.1, J10.3, J10.4, J10.5, J12.A12, J12.B12, J12.SH, R1.2, R2.2, SW1.2
I2S_BCLK_OUT: J2.17, J5.6, J7.2
I2S_DOUT_OUT: J1.10, J5.5, J7.3
I2S_LRCLK_OUT: J2.18, J5.7, J7.4
I2S_SCK_IN: J2.6, J3.1
I2S_SD_IN: J2.8, J4.1
I2S_WS_IN: J2.7, J3.2
MAX_GAIN_AUX: J5.4, J11.2
PCM_SCK_AUX: J7.1, J11.1
PTT_BTN: J2.4, SW1.1
TFT_CS: J1.5, J8.7
TFT_DC: J1.4, J8.6
TFT_MOSI: J1.7, J8.4
TFT_RST: J2.5, J8.5
TFT_SCLK: J1.6, J8.3

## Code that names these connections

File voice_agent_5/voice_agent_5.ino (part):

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// =====================================================================
const int BUTTON_PIN = 1;

static const gpio_num_t I2S_SCK_IN = GPIO_NUM_42;
static const gpio_num_t I2S_WS_IN = GPIO_NUM_41;
static const gpio_num_t I2S_SD_IN = GPIO_NUM_40;

static const gpio_num_t I2S_BCLK_OUT = GPIO_NUM_47;
static const gpio_num_t I2S_LRCLK_OUT = GPIO_NUM_21;
static const gpio_num_t I2S_DOUT_OUT = GPIO_NUM_17;

// Audio output mute pins (PCM5102A + MAX98357A coexistence on shared I2S bus).
// Both default LOW so a half-booted device is silent; apply_audio_output() drives
// HIGH on the selected chip's enable pin. Existing breadboard builds tie MAX SD
// straight to 3.3V and ignore GPIO_NUM_38 entirely — the default selection
// (Speaker) drives GPIO_NUM_38 HIGH so they behave identically.
static const gpio_num_t AUDIO_MAX_SD_PIN   = GPIO_NUM_38;  // MAX98357A SD: HIGH = enabled (stereo-average)
static const gpio_num_t AUDIO_PCM_XSMT_PIN = GPIO_NUM_39;  // PCM5102A XSMT: HIGH = un-muted

enum AudioOutput : uint8_t {
  AUDIO_OUT_SPEAKER    = 0,  // MAX98357A
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
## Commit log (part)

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2026-05-18 release v0.6: emoji customization, voice picker, gpt-realtime-2 GA, PlatformIO
    - in-browser emoji customization via captive portal (PNG/JPG/GIF per emotion)
    - migrate to gpt-realtime-2 (GA) and add voice-selection dropdown
    - raise system-prompt cap to 12 KB; drop temperature field
    - set_volume tool + on-screen volume bar
    - info screen with network details, QR code, auto-dismiss
    - PCB outline + mounting + speaker cutout in enclosure
2026-05-31 release v0.7: Arduino IDE build fix, optional headphone DAC, PCB build/enclosure prep
    - Fix Arduino IDE compile error ('QRCode' not declared) by switching QR
    rendering to the bundled esp_qrcode API; drop ricmoo/QRCode dependency
    - Optional PCM5102A headphone DAC with portal Audio Output selector
    - Enclosure split: ship box3_pcb.stl (PCB build) alongside box3.stl
    - README/toolchain/architecture docs updated
2026-06-01 release v0.8: Comic Pop-Art portal redesign, user/admin split
2026-06-07 release v0.9: persona profiles, Browse gallery, language setting, MP4 emoji
2026-06-07 release v0.10: Historical/Philosophy personas, Browse accordion redesign
